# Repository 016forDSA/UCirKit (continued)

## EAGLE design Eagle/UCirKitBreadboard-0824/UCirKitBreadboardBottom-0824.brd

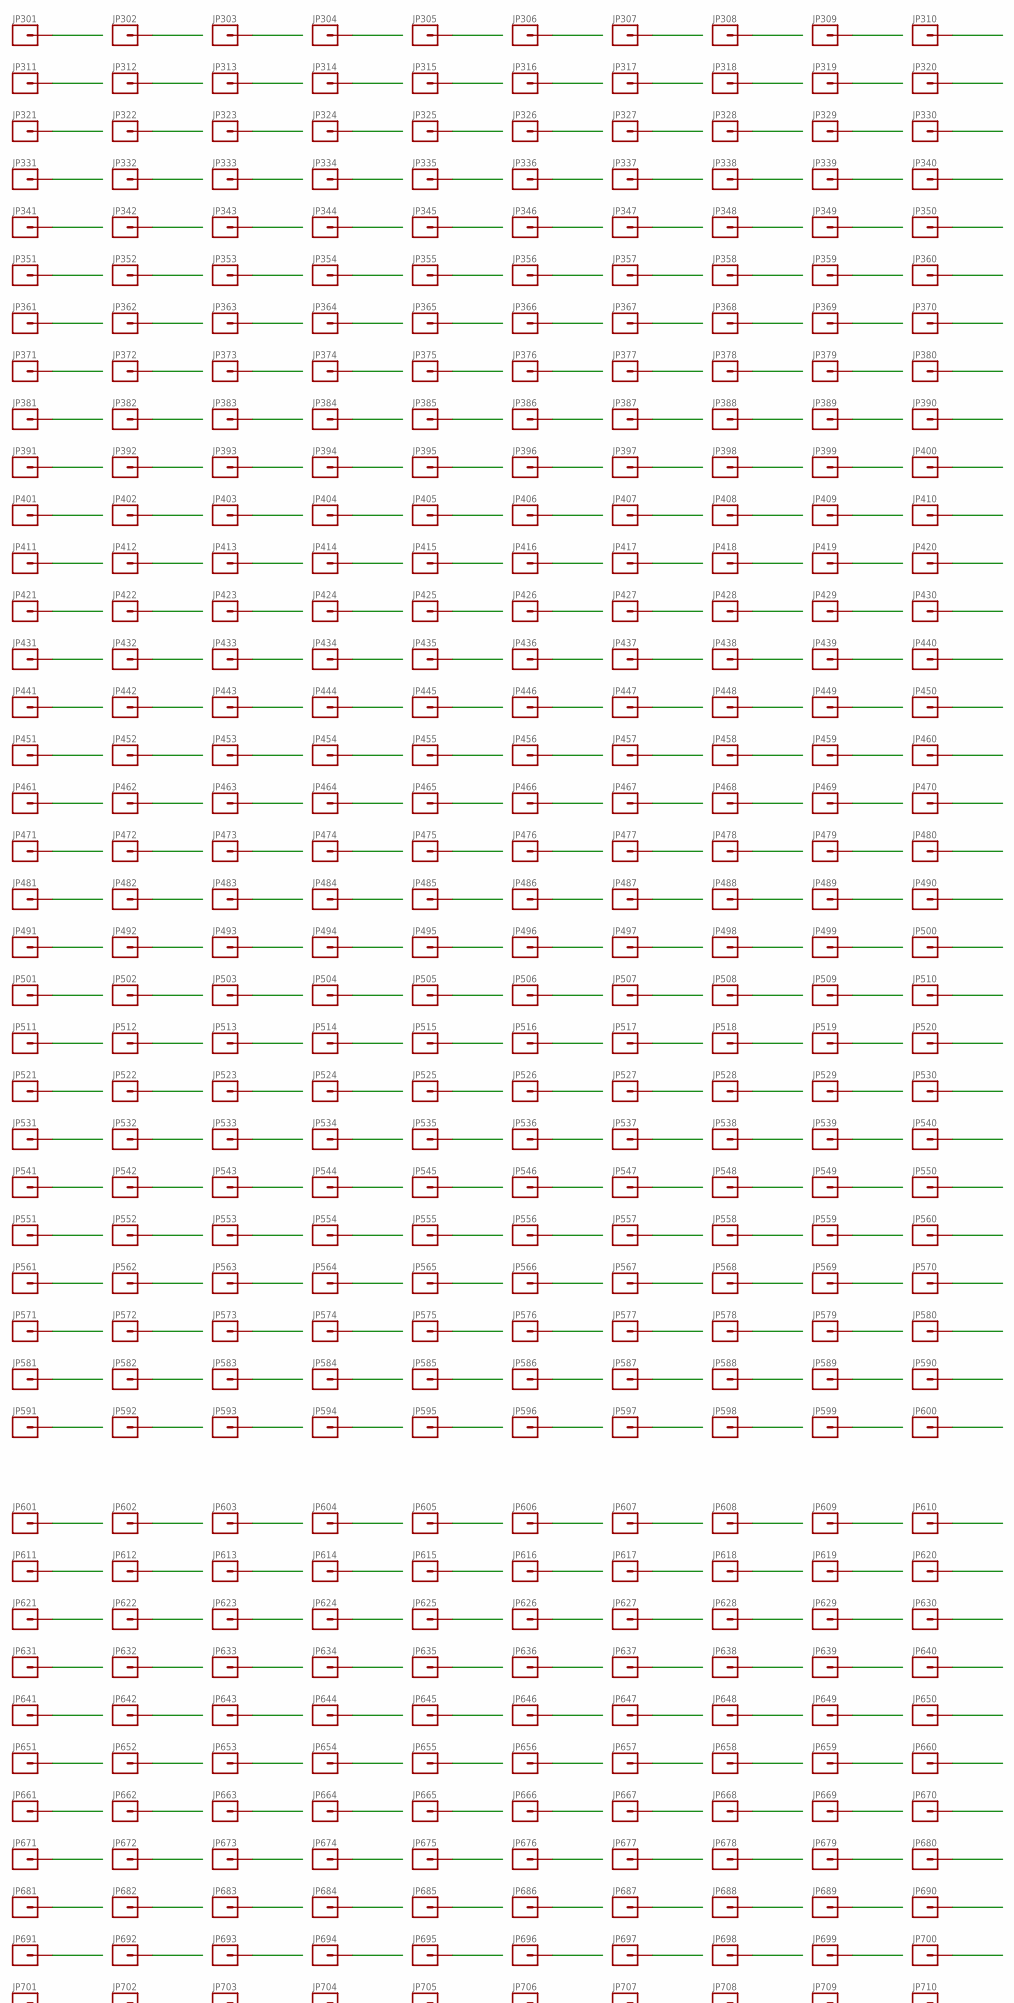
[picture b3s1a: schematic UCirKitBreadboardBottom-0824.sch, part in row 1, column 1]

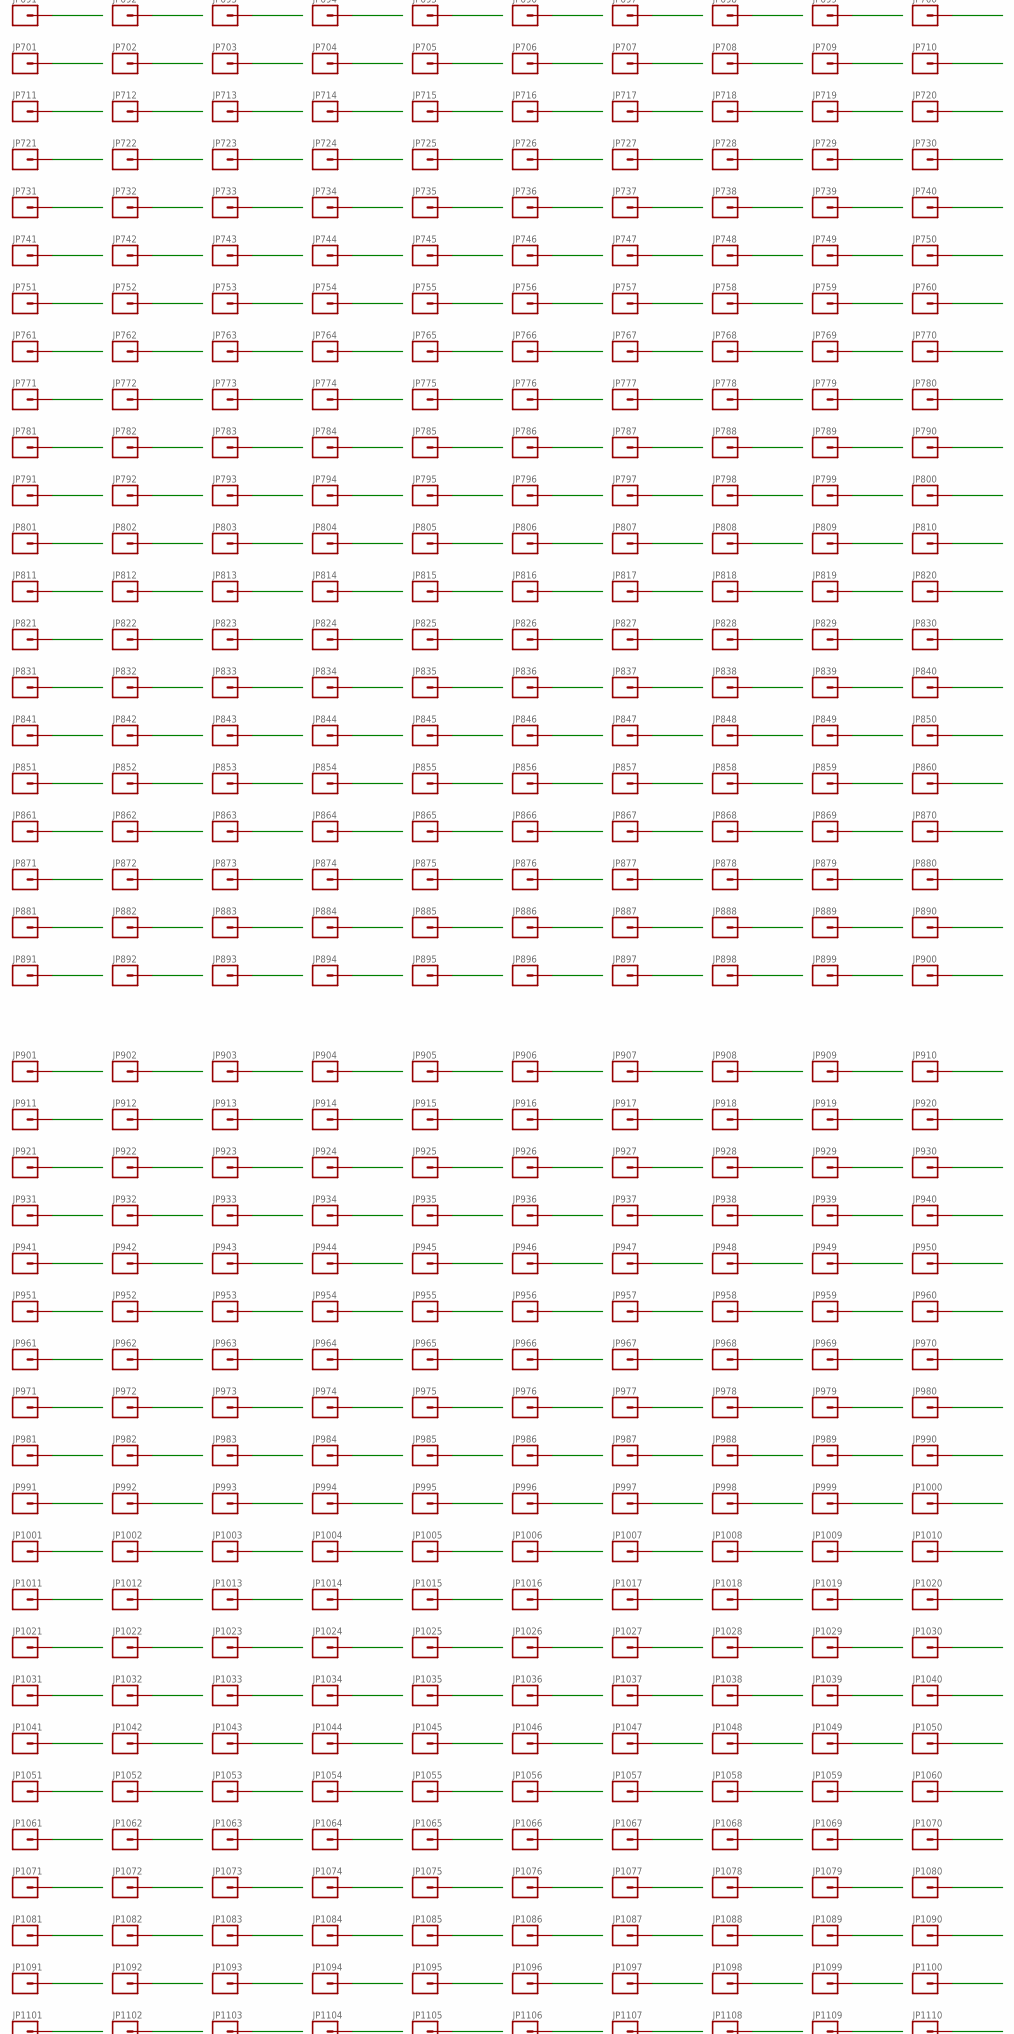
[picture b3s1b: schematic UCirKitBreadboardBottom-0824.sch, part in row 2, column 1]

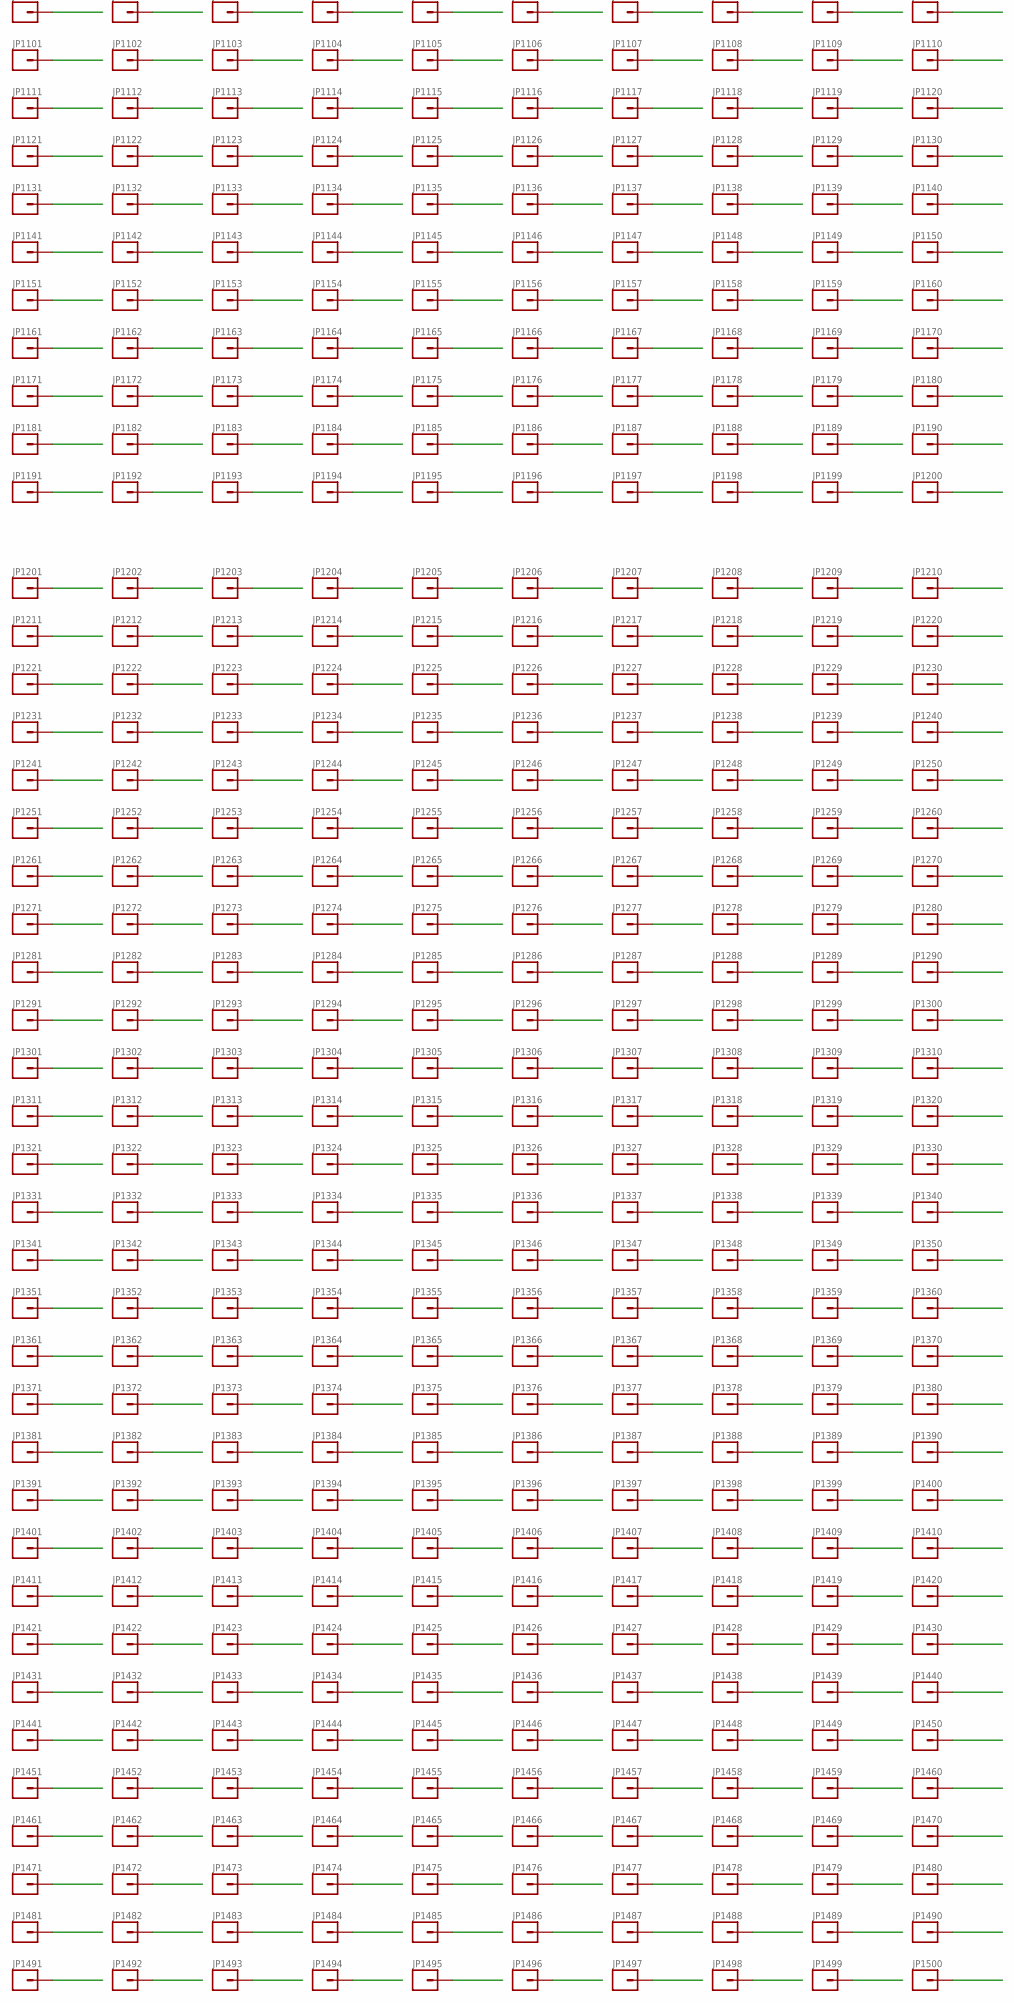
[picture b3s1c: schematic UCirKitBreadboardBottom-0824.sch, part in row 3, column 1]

Parts:
JP301, JP302, JP303, JP304, JP305, JP306, JP307, JP308, JP309, JP310, JP311, JP312, JP313, JP314, JP315, JP316, JP317, JP318, JP319, JP320, JP321, JP322, JP323, JP324, JP325, JP326, JP327, JP328, JP329, JP330, JP331, JP332, JP333, JP334, JP335, JP336, JP337, JP338, JP339, JP340, JP341, JP342, JP343, JP344, JP345, JP346, JP347, JP348, JP349, JP350, JP351, JP352, JP353, JP354, JP355, JP356, JP357, JP358, JP359, JP360, JP361, JP362, JP363, JP364, JP365, JP366, JP367, JP368, JP369, JP370, JP371, JP372, JP373, JP374, JP375, JP376, JP377, JP378, JP379, JP380, JP381, JP382, JP383, JP384, JP385, JP386, JP387, JP388, JP389, JP390, JP391, JP392, JP393, JP394, JP395, JP396, JP397, JP398, JP399, JP400, JP401, JP402, JP403, JP404, JP405, JP406, JP407, JP408, JP409, JP410, JP411, JP412, JP413, JP414, JP415, JP416, JP417, JP418, JP419, JP420, JP421, JP422, JP423, JP424, JP425, JP426, JP427, JP428, JP429, JP430, JP431, JP432, JP433, JP434, JP435, JP436, JP437, JP438, JP439, JP440, JP441, JP442, JP443, JP444, JP445, JP446, JP447, JP448, JP449, JP450, JP451, JP452, JP453, JP454, JP455, JP456, JP457, JP458, JP459, JP460, JP461, JP462, JP463, JP464, JP465, JP466, JP467, JP468, JP469, JP470, JP471, JP472, JP473, JP474, JP475, JP476, JP477, JP478, JP479, JP480, JP481, JP482, JP483, JP484, JP485, JP486, JP487, JP488, JP489, JP490, JP491, JP492, JP493, JP494, JP495, JP496, JP497, JP498, JP499, JP500, JP501, JP502, JP503, JP504, JP505, JP506, JP507, JP508, JP509, JP510, JP511, JP512, JP513, JP514, JP515, JP516, JP517, JP518, JP519, JP520, JP521, JP522, JP523, JP524, JP525, JP526, JP527, JP528, JP529, JP530, JP531, JP532, JP533, JP534, JP535, JP536, JP537, JP538, JP539, JP540, JP541, JP542, JP543, JP544, JP545, JP546, JP547, JP548, JP549, JP550, JP551, JP552, JP553, JP554, JP555, JP556, JP557, JP558, JP559, JP560, JP561, JP562, JP563, JP564, JP565, JP566, JP567, JP568, JP569, JP570, JP571, JP572, JP573, JP574, JP575, JP576, JP577, JP578, JP579, JP580, JP581, JP582, JP583, JP584, JP585, JP586, JP587, JP588, JP589, JP590, JP591, JP592, JP593, JP594, JP595, JP596, JP597, JP598, JP599, JP600, JP601, JP602, JP603, JP604, JP605, JP606, JP607, JP608, JP609, JP610, JP611, JP612, JP613, JP614, JP615, JP616, JP617, JP618, JP619, JP620, JP621, JP622, JP623, JP624, JP625, JP626, JP627, JP628, JP629, JP630, JP631, JP632, JP633, JP634, JP635, JP636, JP637, JP638, JP639, JP640, JP641, JP642, JP643, JP644, JP645, JP646, JP647, JP648, JP649, JP650, JP651, JP652, JP653, JP654, JP655, JP656, JP657, JP658, JP659, JP660, JP661, JP662, JP663, JP664, JP665, JP666, JP667, JP668, JP669, JP670, JP671, JP672, JP673, JP674, JP675, JP676, JP677, JP678, JP679, JP680, JP681, JP682, JP683, JP684, JP685, JP686, JP687, JP688, JP689, JP690, JP691, JP692, JP693, JP694, JP695, JP696, JP697, JP698, JP699, JP700, JP701, JP702, JP703, JP704, JP705, JP706, JP707, JP708, JP709, JP710, JP711, JP712, JP713, JP714, JP715, JP716, JP717, JP718, JP719, JP720, JP721, JP722, JP723, JP724, JP725, JP726, JP727, JP728, JP729, JP730, JP731, JP732, JP733, JP734, JP735, JP736, JP737, JP738, JP739, JP740, JP741, JP742, JP743, JP744, JP745, JP746, JP747, JP748, JP749, JP750, JP751, JP752, JP753, JP754, JP755, JP756, JP757, JP758, JP759, JP760, JP761, JP762, JP763, JP764, JP765, JP766, JP767, JP768, JP769, JP770, JP771, JP772, JP773, JP774, JP775, JP776, JP777, JP778, JP779, JP780, JP781, JP782, JP783, JP784, JP785, JP786, JP787, JP788, JP789, JP790, JP791, JP792, JP793, JP794, JP795, JP796, JP797, JP798, JP799, JP800, JP801, JP802, JP803, JP804, JP805, JP806, JP807, JP808, JP809, JP810, JP811, JP812, JP813, JP814, JP815, JP816, JP817, JP818, JP819, JP820, JP821, JP822, JP823, JP824, JP825, JP826, JP827, JP828, JP829, JP830, JP831, JP832, JP833, JP834, JP835, JP836, JP837, JP838, JP839, JP840, JP841, JP842, JP843, JP844, JP845, JP846, JP847, JP848, JP849, JP850, JP851, JP852, JP853, JP854, JP855, JP856, JP857, JP858, JP859, JP860, JP861, JP862, JP863, JP864, JP865, JP866, JP867, JP868, JP869, JP870, JP871, JP872, JP873, JP874, JP875, JP876, JP877, JP878, JP879, JP880, JP881, JP882, JP883, JP884, JP885, JP886, JP887, JP888, JP889, JP890, JP891, JP892, JP893, JP894, JP895, JP896, JP897, JP898, JP899, JP900, JP901, JP902, JP903, JP904, JP905, JP906, JP907, JP908, JP909, JP910, JP911, JP912, JP913, JP914, JP915, JP916, JP917, JP918, JP919, JP920, JP921, JP922, JP923, JP924, JP925, JP926, JP927, JP928, JP929, JP930, JP931, JP932, JP933, JP934, JP935, JP936, JP937, JP938, JP939, JP940, JP941, JP942, JP943, JP944, JP945, JP946, JP947, JP948, JP949, JP950, JP951, JP952, JP953, JP954, JP955, JP956, JP957, JP958, JP959, JP960, JP961, JP962, JP963, JP964, JP965, JP966, JP967, JP968, JP969, JP970, JP971, JP972, JP973, JP974, JP975, JP976, JP977, JP978, JP979, JP980, JP981, JP982, JP983, JP984, JP985, JP986, JP987, JP988, JP989, JP990, JP991, JP992, JP993, JP994, JP995, JP996, JP997, JP998, JP999, JP1000, JP1001, JP1002, JP1003, JP1004, JP1005, JP1006, JP1007, JP1008, JP1009, JP1010, JP1011, JP1012, JP1013, JP1014, JP1015, JP1016, JP1017, JP1018, JP1019, JP1020, JP1021, JP1022, JP1023, JP1024, JP1025, JP1026, JP1027, JP1028, JP1029, JP1030, JP1031, JP1032, JP1033, JP1034, JP1035, JP1036, JP1037, JP1038, JP1039, JP1040, JP1041, JP1042, JP1043, JP1044, JP1045, JP1046, JP1047, JP1048, JP1049, JP1050, JP1051, JP1052, JP1053, JP1054, JP1055, JP1056, JP1057, JP1058, JP1059, JP1060, JP1061, JP1062, JP1063, JP1064, JP1065, JP1066, JP1067, JP1068, JP1069, JP1070, JP1071, JP1072, JP1073, JP1074, JP1075, JP1076, JP1077, JP1078, JP1079, JP1080, JP1081, JP1082, JP1083, JP1084, JP1085, JP1086, JP1087, JP1088, JP1089, JP1090, JP1091, JP1092, JP1093, JP1094, JP1095, JP1096, JP1097, JP1098, JP1099, JP1100, JP1101, JP1102, JP1103, JP1104, JP1105, JP1106, JP1107, JP1108, JP1109, JP1110, JP1111, JP1112, JP1113, JP1114, JP1115, JP1116, JP1117, JP1118, JP1119, JP1120, JP1121, JP1122, JP1123, JP1124, JP1125, JP1126, JP1127, JP1128, JP1129, JP1130, JP1131, JP1132, JP1133, JP1134, JP1135, JP1136, JP1137, JP1138, JP1139, JP1140, JP1141, JP1142, JP1143, JP1144, JP1145, JP1146, JP1147, JP1148, JP1149, JP1150, JP1151, JP1152, JP1153, JP1154, JP1155, JP1156, JP1157, JP1158, JP1159, JP1160, JP1161, JP1162, JP1163, JP1164, JP1165, JP1166, JP1167, JP1168, JP1169, JP1170, JP1171, JP1172, JP1173, JP1174, JP1175, JP1176, JP1177, JP1178, JP1179, JP1180, JP1181, JP1182, JP1183, JP1184, JP1185, JP1186, JP1187, JP1188, JP1189, JP1190, JP1191, JP1192, JP1193, JP1194, JP1195, JP1196, JP1197, JP1198, JP1199, JP1200, JP1201, JP1202, JP1203, JP1204, JP1205, JP1206, JP1207, JP1208, JP1209, JP1210, JP1211, JP1212, JP1213, JP1214, JP1215, JP1216, JP1217, JP1218, JP1219, JP1220, JP1221, JP1222, JP1223, JP1224, JP1225, JP1226, JP1227, JP1228, JP1229, JP1230, JP1231, JP1232, JP1233, JP1234, JP1235, JP1236, JP1237, JP1238, JP1239, JP1240, JP1241, JP1242, JP1243, JP1244, JP1245, JP1246, JP1247, JP1248, JP1249, JP1250, JP1251, JP1252, JP1253, JP1254, JP1255, JP1256, JP1257, JP1258, JP1259, JP1260, JP1261, JP1262, JP1263, JP1264, JP1265, JP1266, JP1267, JP1268, JP1269, JP1270, JP1271, JP1272, JP1273, JP1274, JP1275, JP1276, JP1277, JP1278, JP1279, JP1280, JP1281, JP1282, JP1283, JP1284, JP1285, JP1286, JP1287, JP1288, JP1289, JP1290, JP1291, JP1292, JP1293, JP1294, JP1295, JP1296, JP1297, JP1298, JP1299, JP1300, JP1301, JP1302, JP1303, JP1304, JP1305, JP1306, JP1307, JP1308, JP1309, JP1310, JP1311, JP1312, JP1313, JP1314, JP1315, JP1316, JP1317, JP1318, JP1319, JP1320, JP1321, JP1322, JP1323, JP1324, JP1325, JP1326, JP1327, JP1328, JP1329, JP1330, JP1331, JP1332, JP1333, JP1334, JP1335, JP1336, JP1337, JP1338, JP1339, JP1340, JP1341, JP1342, JP1343, JP1344, JP1345, JP1346, JP1347, JP1348, JP1349, JP1350, JP1351, JP1352, JP1353, JP1354, JP1355, JP1356, JP1357, JP1358, JP1359, JP1360, JP1361, JP1362, JP1363, JP1364, JP1365, JP1366, JP1367, JP1368, JP1369, JP1370, JP1371, JP1372, JP1373, JP1374, JP1375, JP1376, JP1377, JP1378, JP1379, JP1380, JP1381, JP1382, JP1383, JP1384, JP1385, JP1386, JP1387, JP1388, JP1389, JP1390, JP1391, JP1392, JP1393, JP1394, JP1395, JP1396, JP1397, JP1398, JP1399, JP1400, JP1401, JP1402, JP1403, JP1404, JP1405, JP1406, JP1407, JP1408, JP1409, JP1410, JP1411, JP1412, JP1413, JP1414, JP1415, JP1416, JP1417, JP1418, JP1419, JP1420, JP1421, JP1422, JP1423, JP1424, JP1425, JP1426, JP1427, JP1428, JP1429, JP1430, JP1431, JP1432, JP1433, JP1434, JP1435, JP1436, JP1437, JP1438, JP1439, JP1440, JP1441, JP1442, JP1443, JP1444, JP1445, JP1446, JP1447, JP1448, JP1449, JP1450, JP1451, JP1452, JP1453, JP1454, JP1455, JP1456, JP1457, JP1458, JP1459, JP1460, JP1461, JP1462, JP1463, JP1464, JP1465, JP1466, JP1467, JP1468, JP1469, JP1470, JP1471, JP1472, JP1473, JP1474, JP1475, JP1476, JP1477, JP1478, JP1479, JP1480, JP1481, JP1482, JP1483, JP1484, JP1485, JP1486, JP1487, JP1488, JP1489, JP1490, JP1491, JP1492, JP1493, JP1494, JP1495, JP1496, JP1497, JP1498, JP1499, JP1500: M01PTH_SMD_3.25X0.85MM_NO_SILK; 1X01_SMD_3.25X0.85MM_NO_SILK

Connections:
0_1440389897: JP301.P$1, JP601.P$1, JP961.P$1, JP1261.P$1
0_1440389981: JP305.P$1, JP605.P$1, JP1151.P$1, JP1451.P$1
0_1440390006: JP306.P$1, JP606.P$1, JP1159.P$1, JP1459.P$1
1_1440389897: JP311.P$1, JP611.P$1, JP963.P$1, JP1263.P$1
1_1440389981: JP315.P$1, JP615.P$1, JP1152.P$1, JP1452.P$1
1_1440390006: JP316.P$1, JP616.P$1, JP1160.P$1, JP1460.P$1
2_1440389897: JP321.P$1, JP621.P$1, JP965.P$1, JP1265.P$1
2_1440389981: JP595.P$1, JP895.P$1, JP1181.P$1, JP1481.P$1
2_1440390006: JP596.P$1, JP896.P$1, JP1189.P$1, JP1489.P$1
3_1440389897: JP331.P$1, JP631.P$1, JP967.P$1, JP1267.P$1
3_1440389981: JP585.P$1, JP885.P$1, JP1182.P$1, JP1482.P$1
3_1440390006: JP586.P$1, JP886.P$1, JP1190.P$1, JP1490.P$1
4_1440389897: JP341.P$1, JP641.P$1, JP969.P$1, JP1269.P$1
4_1440389981: JP325.P$1, JP625.P$1, JP1150.P$1, JP1450.P$1
4_1440390006: JP326.P$1, JP626.P$1, JP1158.P$1, JP1458.P$1
5_1440389897: JP351.P$1, JP651.P$1, JP971.P$1, JP1271.P$1
5_1440389981: JP335.P$1, JP635.P$1, JP1153.P$1, JP1453.P$1
5_1440390006: JP336.P$1, JP636.P$1, JP1161.P$1, JP1461.P$1
6_1440389897: JP361.P$1, JP661.P$1, JP973.P$1, JP1273.P$1
6_1440389981: JP575.P$1, JP875.P$1, JP1180.P$1, JP1480.P$1
6_1440390006: JP576.P$1, JP876.P$1, JP1188.P$1, JP1488.P$1
7_1440389897: JP371.P$1, JP671.P$1, JP975.P$1, JP1275.P$1
7_1440389981: JP565.P$1, JP865.P$1, JP1183.P$1, JP1483.P$1
7_1440390006: JP566.P$1, JP866.P$1, JP1191.P$1, JP1491.P$1
8_1440389897: JP381.P$1, JP681.P$1, JP977.P$1, JP1277.P$1
8_1440389981: JP345.P$1, JP645.P$1, JP1149.P$1, JP1449.P$1
8_1440390006: JP346.P$1, JP646.P$1, JP1157.P$1, JP1457.P$1
9_1440389897: JP391.P$1, JP691.P$1, JP979.P$1, JP1279.P$1
9_1440389981: JP355.P$1, JP655.P$1, JP1154.P$1, JP1454.P$1
9_1440390006: JP356.P$1, JP656.P$1, JP1162.P$1, JP1462.P$1
10_1440389897: JP401.P$1, JP701.P$1, JP981.P$1, JP1281.P$1
10_1440389981: JP555.P$1, JP855.P$1, JP1179.P$1, JP1479.P$1
10_1440390006: JP556.P$1, JP856.P$1, JP1187.P$1, JP1487.P$1
11_1440389897: JP411.P$1, JP711.P$1, JP983.P$1, JP1283.P$1
11_1440389981: JP545.P$1, JP845.P$1, JP1184.P$1, JP1484.P$1
11_1440390006: JP546.P$1, JP846.P$1, JP1192.P$1, JP1492.P$1
12_1440389897: JP421.P$1, JP721.P$1, JP985.P$1, JP1285.P$1
12_1440389981: JP365.P$1, JP665.P$1, JP1148.P$1, JP1448.P$1
12_1440390006: JP366.P$1, JP666.P$1, JP1156.P$1, JP1456.P$1
13_1440389897: JP431.P$1, JP731.P$1, JP987.P$1, JP1287.P$1
13_1440389981: JP375.P$1, JP675.P$1, JP1155.P$1, JP1455.P$1
13_1440390006: JP376.P$1, JP676.P$1, JP1163.P$1, JP1463.P$1
14_1440389897: JP441.P$1, JP741.P$1, JP989.P$1, JP1289.P$1
14_1440389981: JP535.P$1, JP835.P$1, JP1178.P$1, JP1478.P$1
14_1440390006: JP386.P$1, JP686.P$1, JP1164.P$1, JP1464.P$1
15_1440389897: JP451.P$1, JP751.P$1, JP991.P$1, JP1291.P$1
15_1440389981: JP525.P$1, JP825.P$1, JP1185.P$1, JP1485.P$1
15_1440390006: JP396.P$1, JP696.P$1, JP1165.P$1, JP1465.P$1
16_1440389897: JP461.P$1, JP761.P$1, JP993.P$1, JP1293.P$1
16_1440389981: JP385.P$1, JP685.P$1, JP1147.P$1, JP1447.P$1
16_1440390006: JP406.P$1, JP706.P$1, JP1166.P$1, JP1466.P$1
17_1440389897: JP471.P$1, JP771.P$1, JP995.P$1, JP1295.P$1
17_1440389981: JP515.P$1, JP815.P$1, JP1177.P$1, JP1477.P$1
17_1440390006: JP416.P$1, JP716.P$1, JP1167.P$1, JP1467.P$1
18_1440389897: JP481.P$1, JP781.P$1, JP997.P$1, JP1297.P$1
18_1440389981: JP395.P$1, JP695.P$1, JP1146.P$1, JP1446.P$1
18_1440390006: JP426.P$1, JP726.P$1, JP1168.P$1, JP1468.P$1
19_1440389897: JP491.P$1, JP791.P$1, JP999.P$1, JP1299.P$1
19_1440389981: JP505.P$1, JP805.P$1, JP1176.P$1, JP1476.P$1
19_1440390006: JP436.P$1, JP736.P$1, JP1169.P$1, JP1469.P$1
20_1440389897: JP501.P$1, JP801.P$1, JP1001.P$1, JP1301.P$1
20_1440389981: JP405.P$1, JP705.P$1, JP1145.P$1, JP1445.P$1
20_1440390006: JP446.P$1, JP746.P$1, JP1170.P$1, JP1470.P$1
21_1440389897: JP511.P$1, JP811.P$1, JP1003.P$1, JP1303.P$1
21_1440389981: JP495.P$1, JP795.P$1, JP1175.P$1, JP1475.P$1
21_1440390006: JP536.P$1, JP836.P$1, JP1186.P$1, JP1486.P$1
22_1440389897: JP521.P$1, JP821.P$1, JP1005.P$1, JP1305.P$1
22_1440389981: JP415.P$1, JP715.P$1, JP1144.P$1, JP1444.P$1
22_1440390006: JP526.P$1, JP826.P$1, JP1193.P$1, JP1493.P$1
23_1440389897: JP531.P$1, JP831.P$1, JP1007.P$1, JP1307.P$1
23_1440389981: JP485.P$1, JP785.P$1, JP1174.P$1, JP1474.P$1
23_1440390006: JP516.P$1, JP816.P$1, JP1194.P$1, JP1494.P$1
24_1440389897: JP541.P$1, JP841.P$1, JP1009.P$1, JP1309.P$1
24_1440389981: JP425.P$1, JP725.P$1, JP1143.P$1, JP1443.P$1
24_1440390006: JP506.P$1, JP806.P$1, JP1195.P$1, JP1495.P$1
25_1440389897: JP551.P$1, JP851.P$1, JP1011.P$1, JP1311.P$1
25_1440389981: JP475.P$1, JP775.P$1, JP1173.P$1, JP1473.P$1
25_1440390006: JP496.P$1, JP796.P$1, JP1196.P$1, JP1496.P$1
26_1440389897: JP561.P$1, JP861.P$1, JP1013.P$1, JP1313.P$1
26_1440389981: JP435.P$1, JP735.P$1, JP1142.P$1, JP1442.P$1
26_1440390006: JP486.P$1, JP786.P$1, JP1197.P$1, JP1497.P$1
27_1440389897: JP571.P$1, JP871.P$1, JP1015.P$1, JP1315.P$1
27_1440389981: JP465.P$1, JP765.P$1, JP1172.P$1, JP1472.P$1
27_1440390006: JP476.P$1, JP776.P$1, JP1198.P$1, JP1498.P$1
28_1440389897: JP581.P$1, JP881.P$1, JP1017.P$1, JP1317.P$1
28_1440389981: JP445.P$1, JP745.P$1, JP1141.P$1, JP1441.P$1
28_1440390006: JP466.P$1, JP766.P$1, JP1199.P$1, JP1499.P$1
29_1440389897: JP591.P$1, JP891.P$1, JP1019.P$1, JP1319.P$1
29_1440389981: JP455.P$1, JP755.P$1, JP1171.P$1, JP1471.P$1
29_1440390006: JP456.P$1, JP756.P$1, JP1200.P$1, JP1500.P$1
30_1440389897: JP592.P$1, JP892.P$1, JP1020.P$1, JP1320.P$1
31_1440389897: JP310.P$1, JP610.P$1, JP1021.P$1, JP1321.P$1
32_1440389897: JP320.P$1, JP620.P$1, JP1023.P$1, JP1323.P$1
33_1440389897: JP330.P$1, JP630.P$1, JP1025.P$1, JP1325.P$1
34_1440389897: JP340.P$1, JP640.P$1, JP1027.P$1, JP1327.P$1
35_1440389897: JP350.P$1, JP650.P$1, JP1029.P$1, JP1329.P$1
36_1440389897: JP360.P$1, JP660.P$1, JP1031.P$1, JP1331.P$1
37_1440389897: JP370.P$1, JP670.P$1, JP1033.P$1, JP1333.P$1
38_1440389897: JP380.P$1, JP680.P$1, JP1035.P$1, JP1335.P$1
39_1440389897: JP390.P$1, JP690.P$1, JP1037.P$1, JP1337.P$1
40_1440389897: JP400.P$1, JP700.P$1, JP1039.P$1, JP1339.P$1
41_1440389897: JP410.P$1, JP710.P$1, JP1041.P$1, JP1341.P$1
42_1440389897: JP420.P$1, JP720.P$1, JP1043.P$1, JP1343.P$1
43_1440389897: JP430.P$1, JP730.P$1, JP1045.P$1, JP1345.P$1
44_1440389897: JP440.P$1, JP740.P$1, JP1047.P$1, JP1347.P$1
45_1440389897: JP450.P$1, JP750.P$1, JP1049.P$1, JP1349.P$1
46_1440389897: JP460.P$1, JP760.P$1, JP1051.P$1, JP1351.P$1
47_1440389897: JP470.P$1, JP770.P$1, JP1053.P$1, JP1353.P$1
48_1440389897: JP480.P$1, JP780.P$1, JP1055.P$1, JP1355.P$1
49_1440389897: JP490.P$1, JP790.P$1, JP1057.P$1, JP1357.P$1
50_1440389897: JP500.P$1, JP800.P$1, JP1059.P$1, JP1359.P$1
51_1440389897: JP510.P$1, JP810.P$1, JP1061.P$1, JP1361.P$1
52_1440389897: JP520.P$1, JP820.P$1, JP1063.P$1, JP1363.P$1
53_1440389897: JP530.P$1, JP830.P$1, JP1065.P$1, JP1365.P$1
54_1440389897: JP540.P$1, JP840.P$1, JP1067.P$1, JP1367.P$1
55_1440389897: JP550.P$1, JP850.P$1, JP1069.P$1, JP1369.P$1
56_1440389897: JP560.P$1, JP860.P$1, JP1071.P$1, JP1371.P$1
57_1440389897: JP570.P$1, JP870.P$1, JP1073.P$1, JP1373.P$1
58_1440389897: JP580.P$1, JP880.P$1, JP1075.P$1, JP1375.P$1
59_1440389897: JP590.P$1, JP890.P$1, JP1077.P$1, JP1377.P$1
60_1440389897: JP600.P$1, JP900.P$1, JP1079.P$1, JP1379.P$1
61_1440389897: JP599.P$1, JP899.P$1, JP1080.P$1, JP1380.P$1
62_1440389897: JP302.P$1, JP602.P$1, JP962.P$1, JP1262.P$1
63_1440389897: JP312.P$1, JP612.P$1, JP964.P$1, JP1264.P$1
64_1440389897: JP322.P$1, JP622.P$1, JP966.P$1, JP1266.P$1
65_1440389897: JP332.P$1, JP632.P$1, JP968.P$1, JP1268.P$1
66_1440389897: JP342.P$1, JP642.P$1, JP970.P$1, JP1270.P$1
67_1440389897: JP352.P$1, JP652.P$1, JP972.P$1, JP1272.P$1
68_1440389897: JP362.P$1, JP662.P$1, JP974.P$1, JP1274.P$1
69_1440389897: JP372.P$1, JP672.P$1, JP976.P$1, JP1276.P$1
70_1440389897: JP382.P$1, JP682.P$1, JP978.P$1, JP1278.P$1
71_1440389897: JP392.P$1, JP692.P$1, JP980.P$1, JP1280.P$1
72_1440389897: JP402.P$1, JP702.P$1, JP982.P$1, JP1282.P$1
73_1440389897: JP412.P$1, JP712.P$1, JP984.P$1, JP1284.P$1
74_1440389897: JP422.P$1, JP722.P$1, JP986.P$1, JP1286.P$1
75_1440389897: JP432.P$1, JP732.P$1, JP988.P$1, JP1288.P$1
76_1440389897: JP442.P$1, JP742.P$1, JP990.P$1, JP1290.P$1
77_1440389897: JP452.P$1, JP752.P$1, JP992.P$1, JP1292.P$1
78_1440389897: JP462.P$1, JP762.P$1, JP994.P$1, JP1294.P$1
79_1440389897: JP472.P$1, JP772.P$1, JP996.P$1, JP1296.P$1
80_1440389897: JP482.P$1, JP782.P$1, JP998.P$1, JP1298.P$1
81_1440389897: JP492.P$1, JP792.P$1, JP1000.P$1, JP1300.P$1
82_1440389897: JP502.P$1, JP802.P$1, JP1002.P$1, JP1302.P$1
83_1440389897: JP512.P$1, JP812.P$1, JP1004.P$1, JP1304.P$1
84_1440389897: JP522.P$1, JP822.P$1, JP1006.P$1, JP1306.P$1
85_1440389897: JP532.P$1, JP832.P$1, JP1008.P$1, JP1308.P$1
86_1440389897: JP542.P$1, JP842.P$1, JP1010.P$1, JP1310.P$1
87_1440389897: JP552.P$1, JP852.P$1, JP1012.P$1, JP1312.P$1
88_1440389897: JP562.P$1, JP862.P$1, JP1014.P$1, JP1314.P$1
89_1440389897: JP572.P$1, JP872.P$1, JP1016.P$1, JP1316.P$1
90_1440389897: JP582.P$1, JP882.P$1, JP1018.P$1, JP1318.P$1
91_1440389897: JP309.P$1, JP609.P$1, JP1022.P$1, JP1322.P$1
92_1440389897: JP319.P$1, JP619.P$1, JP1024.P$1, JP1324.P$1
93_1440389897: JP329.P$1, JP629.P$1, JP1026.P$1, JP1326.P$1
94_1440389897: JP339.P$1, JP639.P$1, JP1028.P$1, JP1328.P$1
95_1440389897: JP349.P$1, JP649.P$1, JP1030.P$1, JP1330.P$1
96_1440389897: JP359.P$1, JP659.P$1, JP1032.P$1, JP1332.P$1
97_1440389897: JP369.P$1, JP669.P$1, JP1034.P$1, JP1334.P$1
98_1440389897: JP379.P$1, JP679.P$1, JP1036.P$1, JP1336.P$1
99_1440389897: JP389.P$1, JP689.P$1, JP1038.P$1, JP1338.P$1
100_1440389897: JP399.P$1, JP699.P$1, JP1040.P$1, JP1340.P$1
101_1440389897: JP409.P$1, JP709.P$1, JP1042.P$1, JP1342.P$1
102_1440389897: JP419.P$1, JP719.P$1, JP1044.P$1, JP1344.P$1
103_1440389897: JP429.P$1, JP729.P$1, JP1046.P$1, JP1346.P$1
104_1440389897: JP439.P$1, JP739.P$1, JP1048.P$1, JP1348.P$1
105_1440389897: JP449.P$1, JP749.P$1, JP1050.P$1, JP1350.P$1
106_1440389897: JP459.P$1, JP759.P$1, JP1052.P$1, JP1352.P$1
107_1440389897: JP469.P$1, JP769.P$1, JP1054.P$1, JP1354.P$1
108_1440389897: JP479.P$1, JP779.P$1, JP1056.P$1, JP1356.P$1
109_1440389897: JP489.P$1, JP789.P$1, JP1058.P$1, JP1358.P$1
110_1440389897: JP499.P$1, JP799.P$1, JP1060.P$1, JP1360.P$1
111_1440389897: JP509.P$1, JP809.P$1, JP1062.P$1, JP1362.P$1
112_1440389897: JP519.P$1, JP819.P$1, JP1064.P$1, JP1364.P$1
113_1440389897: JP529.P$1, JP829.P$1, JP1066.P$1, JP1366.P$1
114_1440389897: JP539.P$1, JP839.P$1, JP1068.P$1, JP1368.P$1
115_1440389897: JP549.P$1, JP849.P$1, JP1070.P$1, JP1370.P$1
116_1440389897: JP559.P$1, JP859.P$1, JP1072.P$1, JP1372.P$1
117_1440389897: JP569.P$1, JP869.P$1, JP1074.P$1, JP1374.P$1
118_1440389897: JP579.P$1, JP879.P$1, JP1076.P$1, JP1376.P$1
119_1440389897: JP589.P$1, JP889.P$1, JP1078.P$1, JP1378.P$1
120_1440389897: JP308.P$1, JP608.P$1, JP1081.P$1, JP1381.P$1
121_1440389897: JP318.P$1, JP618.P$1, JP1083.P$1, JP1383.P$1
122_1440389897: JP328.P$1, JP628.P$1, JP1085.P$1, JP1385.P$1
123_1440389897: JP338.P$1, JP638.P$1, JP1087.P$1, JP1387.P$1
124_1440389897: JP348.P$1, JP648.P$1, JP1089.P$1, JP1389.P$1
125_1440389897: JP358.P$1, JP658.P$1, JP1091.P$1, JP1391.P$1
126_1440389897: JP368.P$1, JP668.P$1, JP1093.P$1, JP1393.P$1
127_1440389897: JP378.P$1, JP678.P$1, JP1095.P$1, JP1395.P$1
128_1440389897: JP388.P$1, JP688.P$1, JP1097.P$1, JP1397.P$1
129_1440389897: JP398.P$1, JP698.P$1, JP1099.P$1, JP1399.P$1
130_1440389897: JP408.P$1, JP708.P$1, JP1101.P$1, JP1401.P$1
131_1440389897: JP418.P$1, JP718.P$1, JP1103.P$1, JP1403.P$1
132_1440389897: JP428.P$1, JP728.P$1, JP1105.P$1, JP1405.P$1
133_1440389897: JP438.P$1, JP738.P$1, JP1107.P$1, JP1407.P$1
134_1440389897: JP448.P$1, JP748.P$1, JP1109.P$1, JP1409.P$1
135_1440389897: JP458.P$1, JP758.P$1, JP1111.P$1, JP1411.P$1
136_1440389897: JP468.P$1, JP768.P$1, JP1113.P$1, JP1413.P$1
137_1440389897: JP478.P$1, JP778.P$1, JP1115.P$1, JP1415.P$1
138_1440389897: JP488.P$1, JP788.P$1, JP1117.P$1, JP1417.P$1
139_1440389897: JP498.P$1, JP798.P$1, JP1119.P$1, JP1419.P$1
140_1440389897: JP508.P$1, JP808.P$1, JP1121.P$1, JP1421.P$1
141_1440389897: JP518.P$1, JP818.P$1, JP1123.P$1, JP1423.P$1
142_1440389897: JP528.P$1, JP828.P$1, JP1125.P$1, JP1425.P$1
143_1440389897: JP538.P$1, JP838.P$1, JP1127.P$1, JP1427.P$1
144_1440389897: JP548.P$1, JP848.P$1, JP1129.P$1, JP1429.P$1
145_1440389897: JP558.P$1, JP858.P$1, JP1131.P$1, JP1431.P$1
146_1440389897: JP568.P$1, JP868.P$1, JP1133.P$1, JP1433.P$1
147_1440389897: JP578.P$1, JP878.P$1, JP1135.P$1, JP1435.P$1
148_1440389897: JP588.P$1, JP888.P$1, JP1137.P$1, JP1437.P$1
149_1440389897: JP598.P$1, JP898.P$1, JP1139.P$1, JP1439.P$1
150_1440389897: JP597.P$1, JP897.P$1, JP1140.P$1, JP1440.P$1
151_1440389897: JP303.P$1, JP603.P$1, JP901.P$1, JP1201.P$1
152_1440389897: JP313.P$1, JP613.P$1, JP903.P$1, JP1203.P$1
153_1440389897: JP323.P$1, JP623.P$1, JP905.P$1, JP1205.P$1
154_1440389897: JP333.P$1, JP633.P$1, JP907.P$1, JP1207.P$1
155_1440389897: JP343.P$1, JP643.P$1, JP909.P$1, JP1209.P$1
156_1440389897: JP353.P$1, JP653.P$1, JP911.P$1, JP1211.P$1
157_1440389897: JP363.P$1, JP663.P$1, JP913.P$1, JP1213.P$1
158_1440389897: JP373.P$1, JP673.P$1, JP915.P$1, JP1215.P$1
159_1440389897: JP383.P$1, JP683.P$1, JP917.P$1, JP1217.P$1
160_1440389897: JP393.P$1, JP693.P$1, JP919.P$1, JP1219.P$1
161_1440389897: JP403.P$1, JP703.P$1, JP921.P$1, JP1221.P$1
162_1440389897: JP413.P$1, JP713.P$1, JP923.P$1, JP1223.P$1
163_1440389897: JP423.P$1, JP723.P$1, JP925.P$1, JP1225.P$1
164_1440389897: JP433.P$1, JP733.P$1, JP927.P$1, JP1227.P$1
165_1440389897: JP443.P$1, JP743.P$1, JP929.P$1, JP1229.P$1
166_1440389897: JP453.P$1, JP753.P$1, JP931.P$1, JP1231.P$1
167_1440389897: JP463.P$1, JP763.P$1, JP933.P$1, JP1233.P$1
168_1440389897: JP473.P$1, JP773.P$1, JP935.P$1, JP1235.P$1
169_1440389897: JP483.P$1, JP783.P$1, JP937.P$1, JP1237.P$1
170_1440389897: JP493.P$1, JP793.P$1, JP939.P$1, JP1239.P$1
171_1440389897: JP503.P$1, JP803.P$1, JP941.P$1, JP1241.P$1
172_1440389897: JP513.P$1, JP813.P$1, JP943.P$1, JP1243.P$1
173_1440389897: JP523.P$1, JP823.P$1, JP945.P$1, JP1245.P$1
174_1440389897: JP533.P$1, JP833.P$1, JP947.P$1, JP1247.P$1
175_1440389897: JP543.P$1, JP843.P$1, JP949.P$1, JP1249.P$1
176_1440389897: JP553.P$1, JP853.P$1, JP951.P$1, JP1251.P$1
177_1440389897: JP563.P$1, JP863.P$1, JP953.P$1, JP1253.P$1
178_1440389897: JP573.P$1, JP873.P$1, JP955.P$1, JP1255.P$1
179_1440389897: JP583.P$1, JP883.P$1, JP957.P$1, JP1257.P$1
180_1440389897: JP593.P$1, JP893.P$1, JP959.P$1, JP1259.P$1
181_1440389897: JP594.P$1, JP894.P$1, JP960.P$1, JP1260.P$1
182_1440389897: JP307.P$1, JP607.P$1, JP1082.P$1, JP1382.P$1
183_1440389897: JP317.P$1, JP617.P$1, JP1084.P$1, JP1384.P$1
184_1440389897: JP327.P$1, JP627.P$1, JP1086.P$1, JP1386.P$1
185_1440389897: JP337.P$1, JP637.P$1, JP1088.P$1, JP1388.P$1
186_1440389897: JP347.P$1, JP647.P$1, JP1090.P$1, JP1390.P$1
187_1440389897: JP357.P$1, JP657.P$1, JP1092.P$1, JP1392.P$1
188_1440389897: JP367.P$1, JP667.P$1, JP1094.P$1, JP1394.P$1
189_1440389897: JP377.P$1, JP677.P$1, JP1096.P$1, JP1396.P$1
190_1440389897: JP387.P$1, JP687.P$1, JP1098.P$1, JP1398.P$1
191_1440389897: JP397.P$1, JP697.P$1, JP1100.P$1, JP1400.P$1
192_1440389897: JP407.P$1, JP707.P$1, JP1102.P$1, JP1402.P$1
193_1440389897: JP417.P$1, JP717.P$1, JP1104.P$1, JP1404.P$1
194_1440389897: JP427.P$1, JP727.P$1, JP1106.P$1, JP1406.P$1
195_1440389897: JP437.P$1, JP737.P$1, JP1108.P$1, JP1408.P$1
196_1440389897: JP447.P$1, JP747.P$1, JP1110.P$1, JP1410.P$1
197_1440389897: JP457.P$1, JP757.P$1, JP1112.P$1, JP1412.P$1
198_1440389897: JP467.P$1, JP767.P$1, JP1114.P$1, JP1414.P$1
199_1440389897: JP477.P$1, JP777.P$1, JP1116.P$1, JP1416.P$1
200_1440389897: JP487.P$1, JP787.P$1, JP1118.P$1, JP1418.P$1
201_1440389897: JP497.P$1, JP797.P$1, JP1120.P$1, JP1420.P$1
202_1440389897: JP507.P$1, JP807.P$1, JP1122.P$1, JP1422.P$1
203_1440389897: JP517.P$1, JP817.P$1, JP1124.P$1, JP1424.P$1
204_1440389897: JP527.P$1, JP827.P$1, JP1126.P$1, JP1426.P$1
205_1440389897: JP537.P$1, JP837.P$1, JP1128.P$1, JP1428.P$1
206_1440389897: JP547.P$1, JP847.P$1, JP1130.P$1, JP1430.P$1
207_1440389897: JP557.P$1, JP857.P$1, JP1132.P$1, JP1432.P$1
208_1440389897: JP567.P$1, JP867.P$1, JP1134.P$1, JP1434.P$1
209_1440389897: JP577.P$1, JP877.P$1, JP1136.P$1, JP1436.P$1
210_1440389897: JP587.P$1, JP887.P$1, JP1138.P$1, JP1438.P$1
211_1440389897: JP304.P$1, JP604.P$1, JP902.P$1, JP1202.P$1
212_1440389897: JP314.P$1, JP614.P$1, JP904.P$1, JP1204.P$1
213_1440389897: JP324.P$1, JP624.P$1, JP906.P$1, JP1206.P$1
214_1440389897: JP334.P$1, JP634.P$1, JP908.P$1, JP1208.P$1
215_1440389897: JP344.P$1, JP644.P$1, JP910.P$1, JP1210.P$1
216_1440389897: JP354.P$1, JP654.P$1, JP912.P$1, JP1212.P$1
217_1440389897: JP364.P$1, JP664.P$1, JP914.P$1, JP1214.P$1
218_1440389897: JP374.P$1, JP674.P$1, JP916.P$1, JP1216.P$1
219_1440389897: JP384.P$1, JP684.P$1, JP918.P$1, JP1218.P$1
220_1440389897: JP394.P$1, JP694.P$1, JP920.P$1, JP1220.P$1
221_1440389897: JP404.P$1, JP704.P$1, JP922.P$1, JP1222.P$1
222_1440389897: JP414.P$1, JP714.P$1, JP924.P$1, JP1224.P$1
223_1440389897: JP424.P$1, JP724.P$1, JP926.P$1, JP1226.P$1
224_1440389897: JP434.P$1, JP734.P$1, JP928.P$1, JP1228.P$1
225_1440389897: JP444.P$1, JP744.P$1, JP930.P$1, JP1230.P$1
226_1440389897: JP454.P$1, JP754.P$1, JP932.P$1, JP1232.P$1
227_1440389897: JP464.P$1, JP764.P$1, JP934.P$1, JP1234.P$1
228_1440389897: JP474.P$1, JP774.P$1, JP936.P$1, JP1236.P$1
229_1440389897: JP484.P$1, JP784.P$1, JP938.P$1, JP1238.P$1
230_1440389897: JP494.P$1, JP794.P$1, JP940.P$1, JP1240.P$1
231_1440389897: JP504.P$1, JP804.P$1, JP942.P$1, JP1242.P$1
232_1440389897: JP514.P$1, JP814.P$1, JP944.P$1, JP1244.P$1
233_1440389897: JP524.P$1, JP824.P$1, JP946.P$1, JP1246.P$1
234_1440389897: JP534.P$1, JP834.P$1, JP948.P$1, JP1248.P$1
235_1440389897: JP544.P$1, JP844.P$1, JP950.P$1, JP1250.P$1
236_1440389897: JP554.P$1, JP854.P$1, JP952.P$1, JP1252.P$1
237_1440389897: JP564.P$1, JP864.P$1, JP954.P$1, JP1254.P$1
238_1440389897: JP574.P$1, JP874.P$1, JP956.P$1, JP1256.P$1
239_1440389897: JP584.P$1, JP884.P$1, JP958.P$1, JP1258.P$1
